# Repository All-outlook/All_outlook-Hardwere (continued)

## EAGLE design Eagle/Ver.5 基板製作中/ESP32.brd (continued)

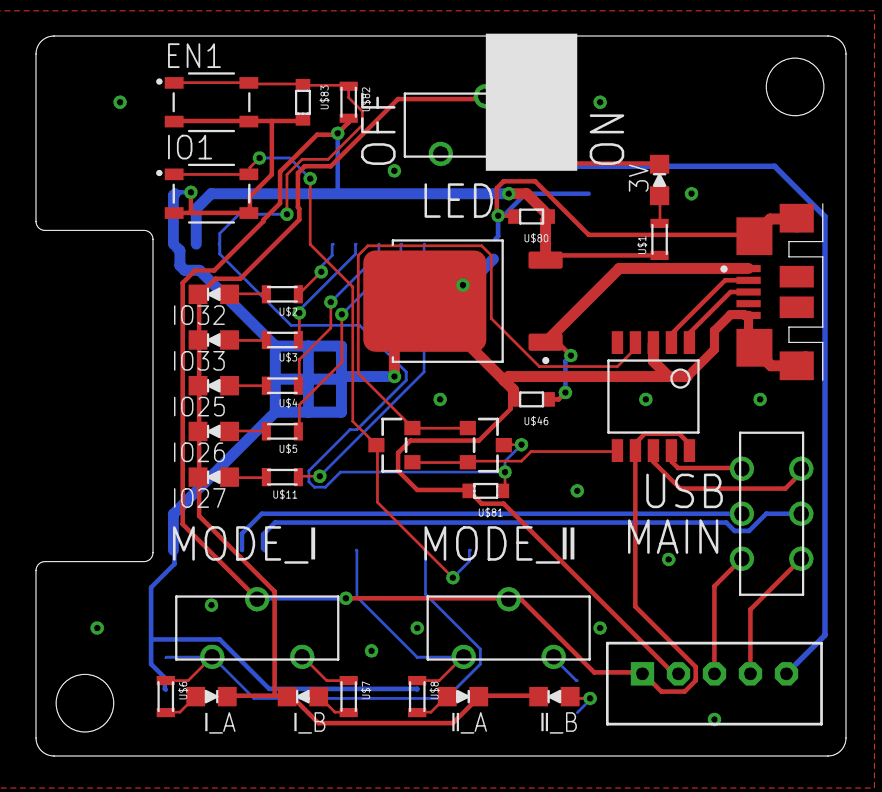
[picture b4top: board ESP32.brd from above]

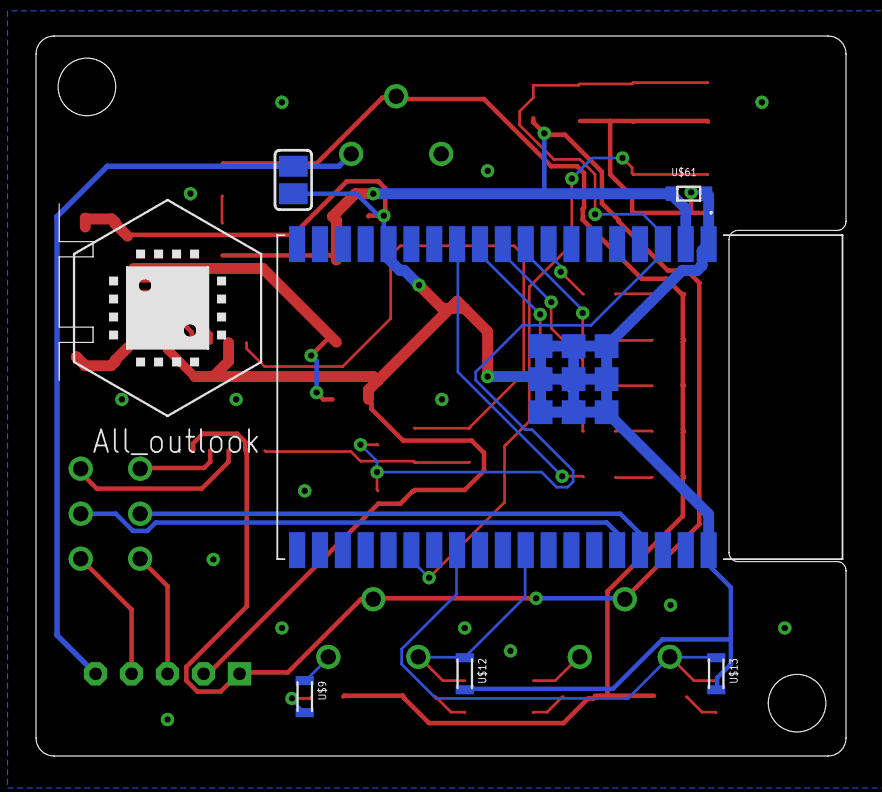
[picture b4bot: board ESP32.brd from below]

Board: 2 copper layers, 45.0 x 40.0 mm, 43 parts (7 on the bottom side), 36 nets.

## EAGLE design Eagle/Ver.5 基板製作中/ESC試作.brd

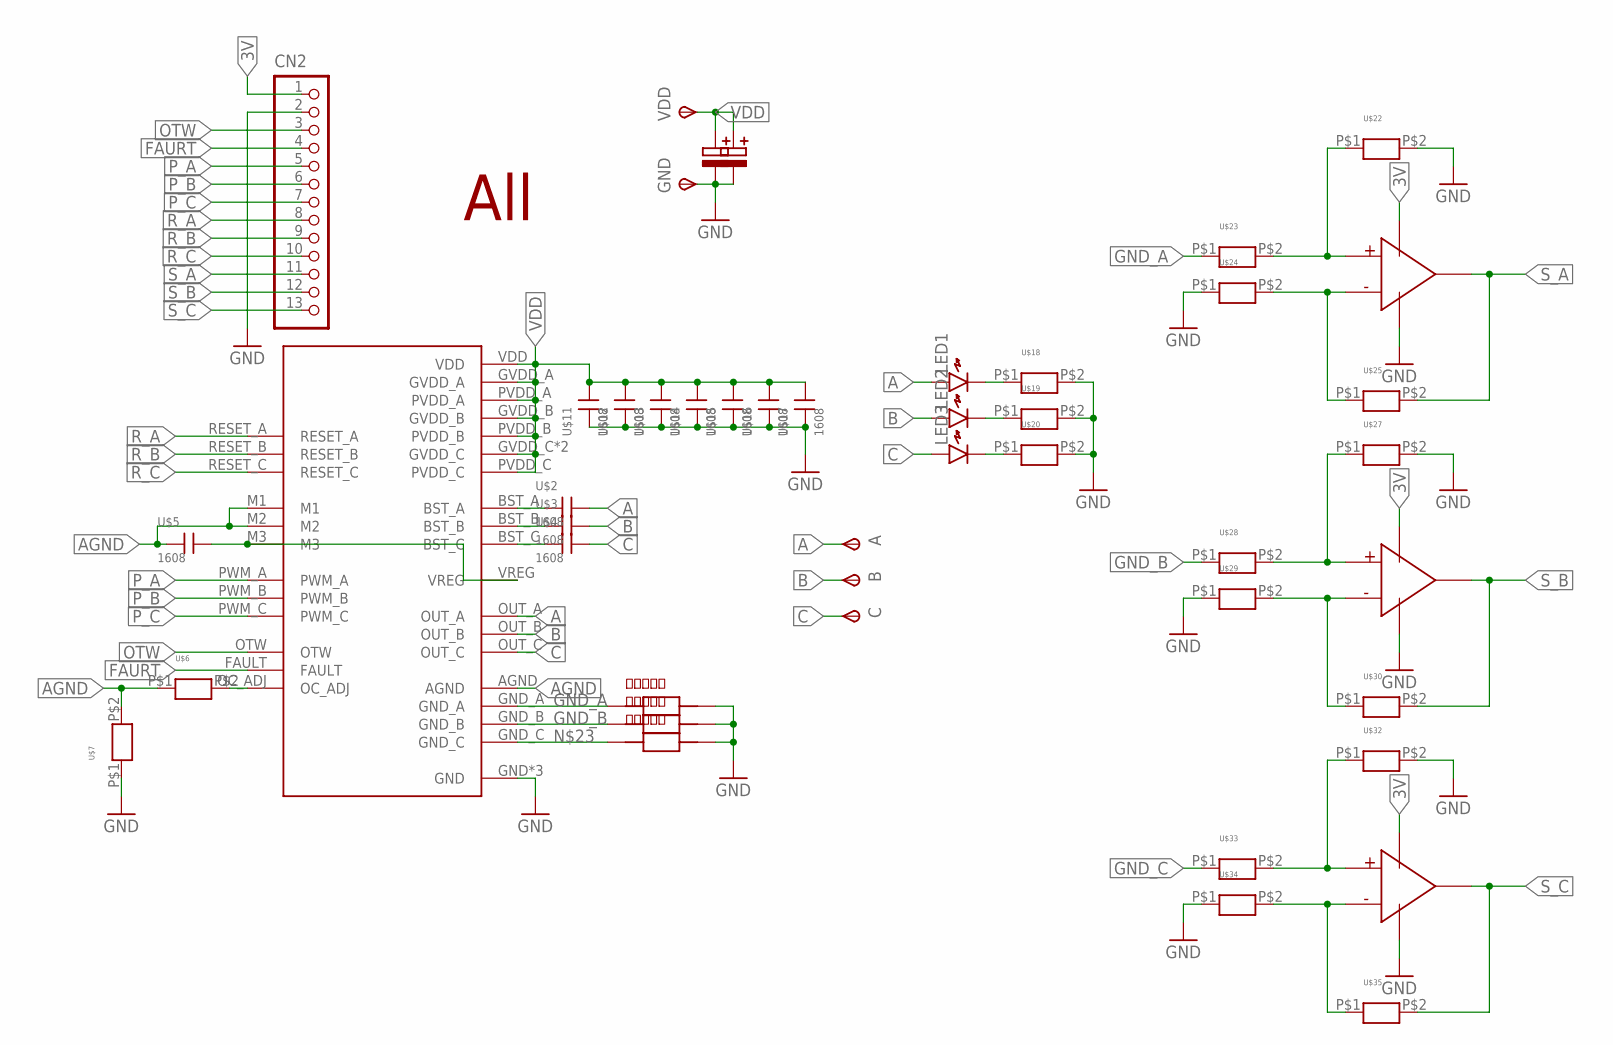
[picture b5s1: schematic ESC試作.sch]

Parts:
A: TPSPAD1-20; P1-20
B: TPSPAD1-20; P1-20
C: TPSPAD1-20; P1-20
CN2: B13B-XH-A
GND: TPSPAD1-20; P1-20
LED1, LED2, LED3: LED1608
U$1: DRV8332
U$2, U$3, U$4, U$5, U$11, U$12, U$13, U$14, U$15, U$16, U$17: 1608; CON
U$6, U$7, U$18, U$19, U$20, U$22, U$23, U$24, U$25, U$27, U$28, U$29, U$30, U$32, U$33, U$34, U$35: R; 1608
U$8, U$9, U$10: R0.1
U$21, U$26, U$31: 77701
U$36, U$37: 25V100
U$38: ALL
VDD: TPSPAD1-20; P1-20

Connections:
3V: CN2.1, U$21.VIN, U$26.VIN, U$31.VIN
A: A.TP, LED1.A, U$1.OUT_A, U$2.P$1 (1)
AGND: U$1.AGND, U$1.M1, U$1.M2, U$5.P$2 (2), U$6.P$1, U$7.P$2
B: B.TP, LED2.A, U$1.OUT_B, U$3.P$1 (1)
C: C.TP, LED3.A, U$1.OUT_C, U$4.P$1 (1)
FAURT: CN2.4, U$1.FAULT
GND: CN2.2, GND.TP, U$1.GND, U$1.GND1 (GND), U$1.GND2 (GND), U$7.P$1, U$8.P$2, U$9.P$2, U$10.P$2, U$11.P$2 (2), U$12.P$2 (2), U$13.P$2 (2), U$14.P$2 (2), U$15.P$2 (2), U$16.P$2 (2), U$17.P$2 (2), U$18.P$2, U$19.P$2, U$20.P$2, U$21.VOUT, U$22.P$2, U$24.P$1, U$26.VOUT, U$27.P$2, U$29.P$1, U$31.VOUT, U$32.P$2, U$34.P$1, U$36.P$2, U$37.P$2
GND_A: U$1.GND_A, U$8.P$1, U$23.P$1
GND_B: U$1.GND_B, U$9.P$1, U$28.P$1
GND_C: U$33.P$1
unnamed: U$21.+, U$22.P$1, U$23.P$2
unnamed: U$21.-, U$24.P$2, U$25.P$1
unnamed: U$1.M3, U$1.VREG, U$5.P$1 (1)
unnamed: LED3.K, U$20.P$1
unnamed: LED2.K, U$19.P$1
unnamed: LED1.K, U$18.P$1
unnamed: U$26.+, U$27.P$1, U$28.P$2
unnamed: U$26.-, U$29.P$2, U$30.P$1
unnamed: U$31.+, U$32.P$1, U$33.P$2
unnamed: U$31.-, U$34.P$2, U$35.P$1
unnamed: U$1.GND_C, U$10.P$1
unnamed: U$1.BST_A, U$2.P$2 (2)
unnamed: U$1.BST_B, U$3.P$2 (2)
unnamed: U$1.BST_C, U$4.P$2 (2)
unnamed: U$1.OC_ADJ, U$6.P$2
OTW: CN2.3, U$1.OTW
P_A: CN2.5, U$1.PWM_A
P_B: CN2.6, U$1.PWM_B
P_C: CN2.7, U$1.PWM_C
R_A: CN2.8, U$1.RESET_A
R_B: CN2.9, U$1.RESET_B
R_C: CN2.10, U$1.RESET_C
S_A: CN2.11, U$21.O, U$25.P$2
S_B: CN2.12, U$26.O, U$30.P$2
S_C: CN2.13, U$31.O, U$35.P$2
VDD: U$1.GVDD_A, U$1.GVDD_B, U$1.GVDD_C, U$1.GVDD_C2 (GVDD_C), U$1.PVDD_A, U$1.PVDD_B, U$1.PVDD_C, U$1.VDD, U$11.P$1 (1), U$12.P$1 (1), U$13.P$1 (1), U$14.P$1 (1), U$15.P$1 (1), U$16.P$1 (1), U$17.P$1 (1), U$36.P$1, U$37.P$1, VDD.TP

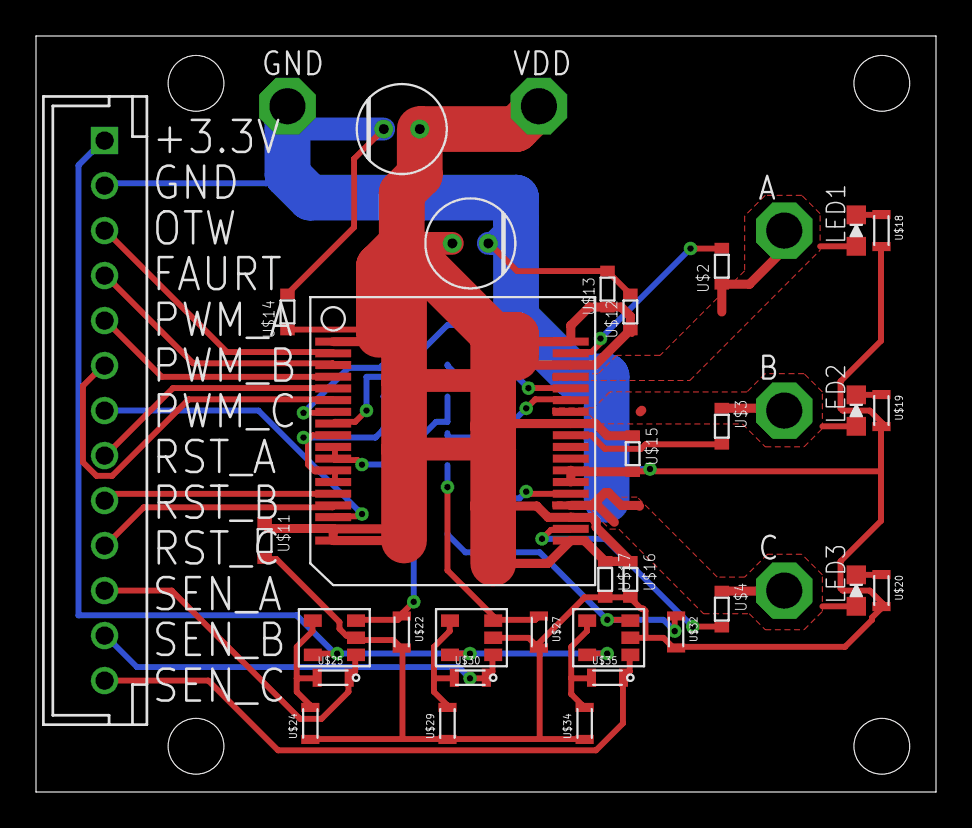
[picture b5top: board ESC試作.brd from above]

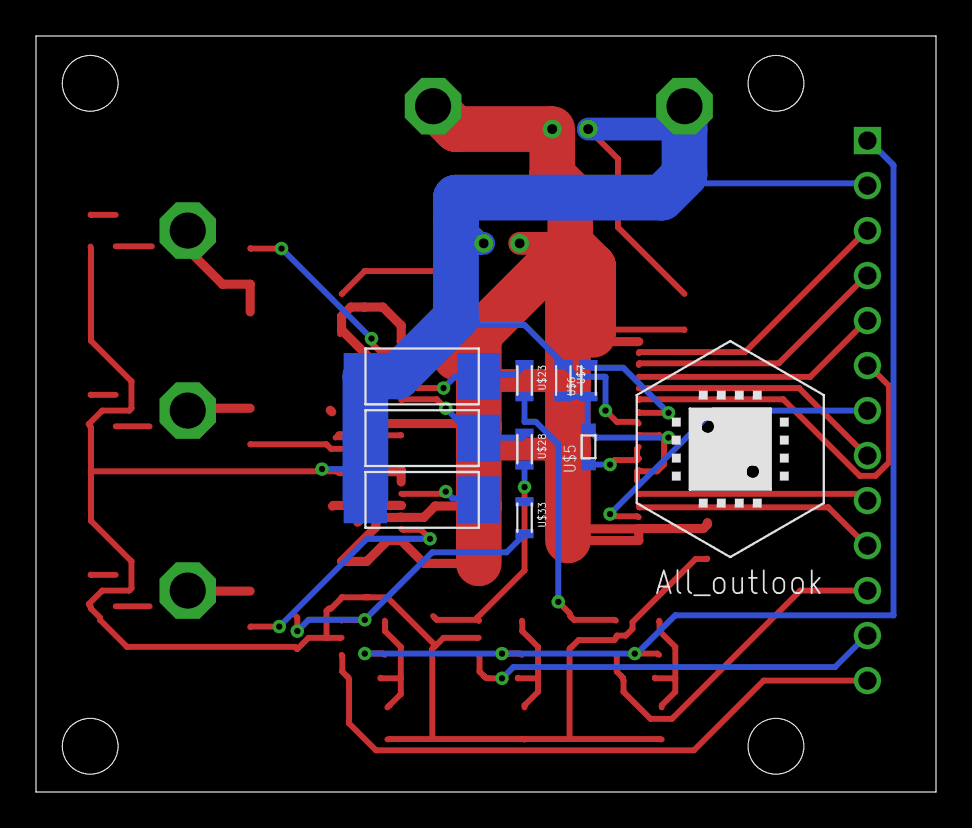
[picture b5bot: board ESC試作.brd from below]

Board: 2 copper layers, 50.0 x 42.0 mm, 47 parts (10 on the bottom side), 35 nets.

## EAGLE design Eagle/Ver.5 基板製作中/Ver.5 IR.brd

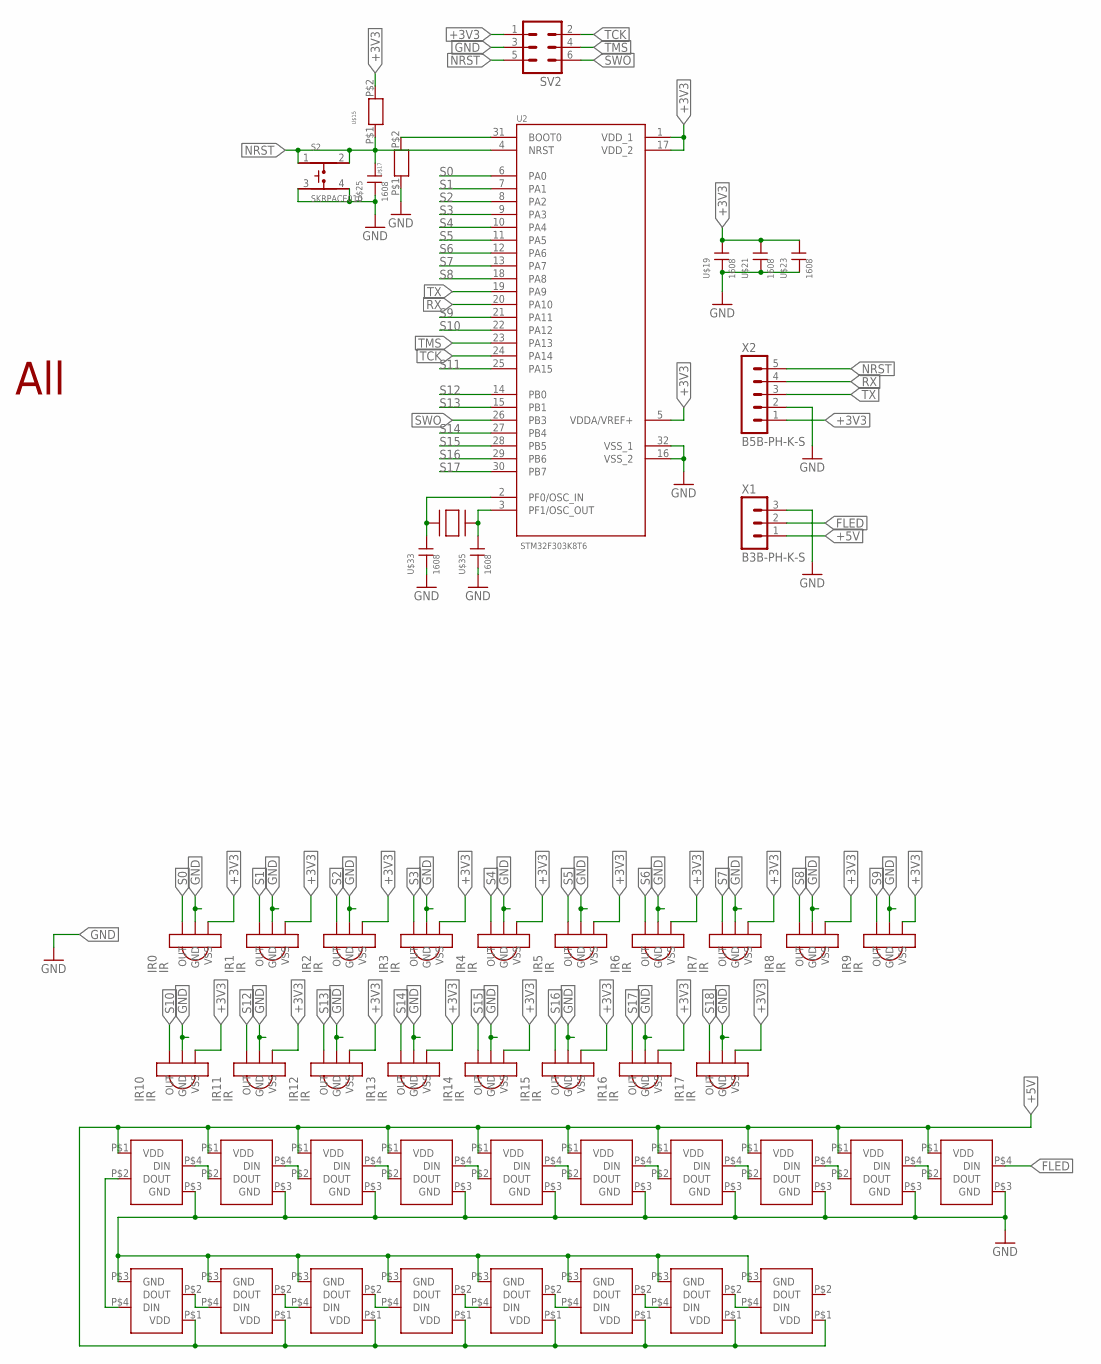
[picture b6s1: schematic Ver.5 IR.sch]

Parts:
F0, F1, F2, F3, F4, F5, F6, F7, F8, F9, F10, F11, F12, F13, F14, F15, F16, F17: LED
IR0, IR1, IR2, IR3, IR4, IR5, IR6, IR7, IR8, IR9, IR10, IR11, IR12, IR13, IR14, IR15, IR16, IR17: IR
S2: SKRPACE010; SW_SKRPACE010
SV2: ML6
U2: STM32F303K8T6; QFP80P900X900X160-32N
U$1: ALL
U$15, U$17: R; 1608
U$19, U$21, U$23, U$25, U$33, U$35: 1608; CON
U$27: SUISYOU; 水晶
X1: B3B-PH-K-S
X2: B5B-PH-K-S

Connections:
+3V3: IR0.P$3 (VSS), IR1.P$3 (VSS), IR2.P$3 (VSS), IR3.P$3 (VSS), IR4.P$3 (VSS), IR5.P$3 (VSS), IR6.P$3 (VSS), IR7.P$3 (VSS), IR8.P$3 (VSS), IR9.P$3 (VSS), IR10.P$3 (VSS), IR11.P$3 (VSS), IR12.P$3 (VSS), IR13.P$3 (VSS), IR14.P$3 (VSS), IR15.P$3 (VSS), IR16.P$3 (VSS), IR17.P$3 (VSS), SV2.1, U2.1 (VDD_1), U2.5 (VDDA/VREF+), U2.17 (VDD_2), U$15.P$2, U$19.P$1 (1), U$21.P$1 (1), U$23.P$1 (1), X2.1
+5V: F0.P$1 (VDD), F1.P$1 (VDD), F2.P$1 (VDD), F3.P$1 (VDD), F4.P$1 (VDD), F5.P$1 (VDD), F6.P$1 (VDD), F7.P$1 (VDD), F8.P$1 (VDD), F9.P$1 (VDD), F10.P$1 (VDD), F11.P$1 (VDD), F12.P$1 (VDD), F13.P$1 (VDD), F14.P$1 (VDD), F15.P$1 (VDD), F16.P$1 (VDD), F17.P$1 (VDD), X1.1
FLED: F0.P$4 (DIN), X1.2
GND: F0.P$3 (GND), F1.P$3 (GND), F2.P$3 (GND), F3.P$3 (GND), F4.P$3 (GND), F5.P$3 (GND), F6.P$3 (GND), F7.P$3 (GND), F8.P$3 (GND), F9.P$3 (GND), F10.P$3 (GND), F11.P$3 (GND), F12.P$3 (GND), F13.P$3 (GND), F14.P$3 (GND), F15.P$3 (GND), F16.P$3 (GND), F17.P$3 (GND), IR0.P$2 (GND), IR1.P$2 (GND), IR2.P$2 (GND), IR3.P$2 (GND), IR4.P$2 (GND), IR5.P$2 (GND), IR6.P$2 (GND), IR7.P$2 (GND), IR8.P$2 (GND), IR9.P$2 (GND), IR10.P$2 (GND), IR11.P$2 (GND), IR12.P$2 (GND), IR13.P$2 (GND), IR14.P$2 (GND), IR15.P$2 (GND), IR16.P$2 (GND), IR17.P$2 (GND), S2.3, S2.4, SV2.3, U2.16 (VSS_2), U2.32 (VSS_1), U$17.P$1, U$19.P$2 (2), U$21.P$2 (2), U$23.P$2 (2), U$25.P$2 (2), U$33.P$2 (2), U$35.P$2 (2), X1.3, X2.2
unnamed: F14.P$2 (DOUT), F15.P$4 (DIN)
unnamed: F13.P$2 (DOUT), F14.P$4 (DIN)
unnamed: F11.P$2 (DOUT), F12.P$4 (DIN)
unnamed: F10.P$2 (DOUT), F11.P$4 (DIN)
unnamed: F8.P$2 (DOUT), F9.P$4 (DIN)
unnamed: F7.P$2 (DOUT), F8.P$4 (DIN)
unnamed: F5.P$2 (DOUT), F6.P$4 (DIN)
unnamed: F4.P$2 (DOUT), F5.P$4 (DIN)
unnamed: F2.P$2 (DOUT), F3.P$4 (DIN)
unnamed: F1.P$2 (DOUT), F2.P$4 (DIN)
unnamed: F0.P$2 (DOUT), F1.P$4 (DIN)
unnamed: F3.P$2 (DOUT), F4.P$4 (DIN)
unnamed: F6.P$2 (DOUT), F7.P$4 (DIN)
unnamed: F9.P$2 (DOUT), F10.P$4 (DIN)
unnamed: F16.P$2 (DOUT), F17.P$4 (DIN)
unnamed: F15.P$2 (DOUT), F16.P$4 (DIN)
unnamed: F12.P$2 (DOUT), F13.P$4 (DIN)
unnamed: U2.31 (BOOT0), U$17.P$2
unnamed: U2.2 (PF0/OSC_IN), U$27.P$1, U$33.P$1 (1)
unnamed: U2.3 (PF1/OSC_OUT), U$27.P$2, U$35.P$1 (1)
NRST: S2.1, S2.2, SV2.5, U2.4 (NRST), U$15.P$1, U$25.P$1 (1), X2.5
RX: U2.20 (PA10), X2.4
S0: IR0.P$1 (OUT), U2.6 (PA0)
S1: IR1.P$1 (OUT), U2.7 (PA1)
S2: IR2.P$1 (OUT), U2.8 (PA2)
S3: IR3.P$1 (OUT), U2.9 (PA3)
S4: IR4.P$1 (OUT), U2.10 (PA4)
S5: IR5.P$1 (OUT), U2.11 (PA5)
S6: IR6.P$1 (OUT), U2.12 (PA6)
S7: IR7.P$1 (OUT), U2.13 (PA7)
S8: IR8.P$1 (OUT), U2.18 (PA8)
S9: IR9.P$1 (OUT), U2.21 (PA11)
S10: IR10.P$1 (OUT), U2.22 (PA12)
S11: U2.25 (PA15)
S12: IR11.P$1 (OUT), U2.14 (PB0)
S13: IR12.P$1 (OUT), U2.15 (PB1)
S14: IR13.P$1 (OUT), U2.27 (PB4)
S15: IR14.P$1 (OUT), U2.28 (PB5)
S16: IR15.P$1 (OUT), U2.29 (PB6)
S17: IR16.P$1 (OUT), U2.30 (PB7)
S18: IR17.P$1 (OUT)
SWO: SV2.6, U2.26 (PB3)
TCK: SV2.2, U2.24 (PA14)
TMS: SV2.4, U2.23 (PA13)
TX: U2.19 (PA9), X2.3

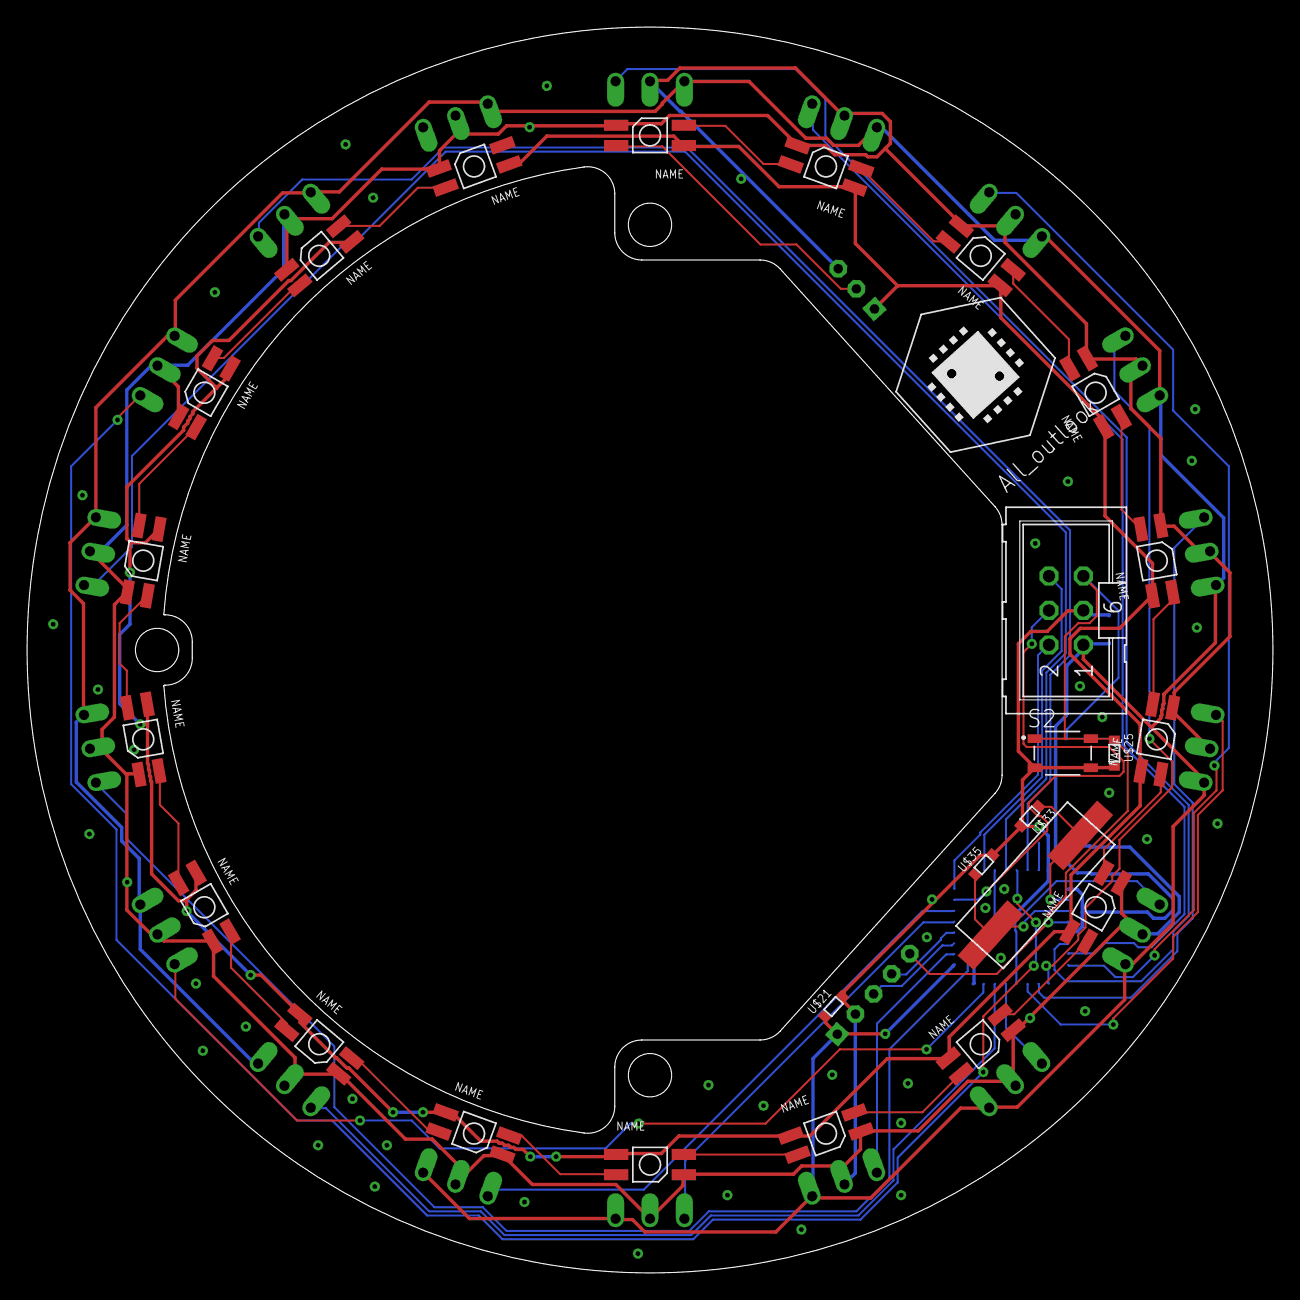
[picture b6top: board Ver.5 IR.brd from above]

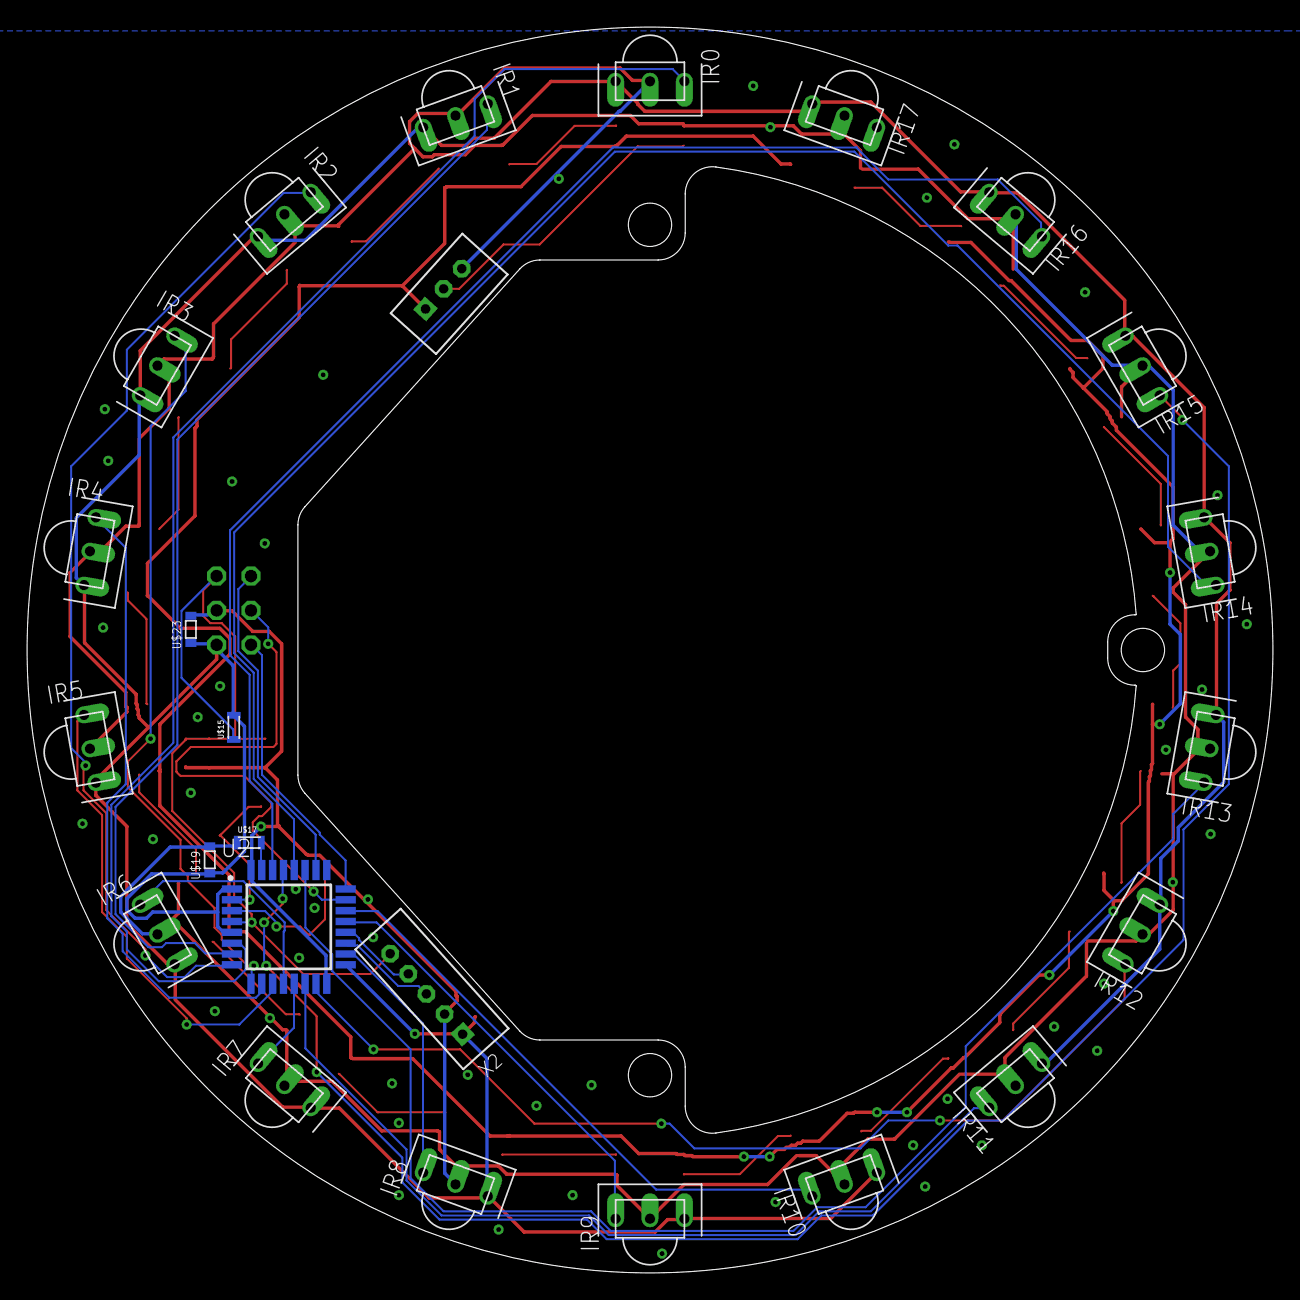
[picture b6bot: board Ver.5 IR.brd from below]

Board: 2 copper layers, 92.0 x 92.0 mm, 51 parts (25 on the bottom side), 47 nets.

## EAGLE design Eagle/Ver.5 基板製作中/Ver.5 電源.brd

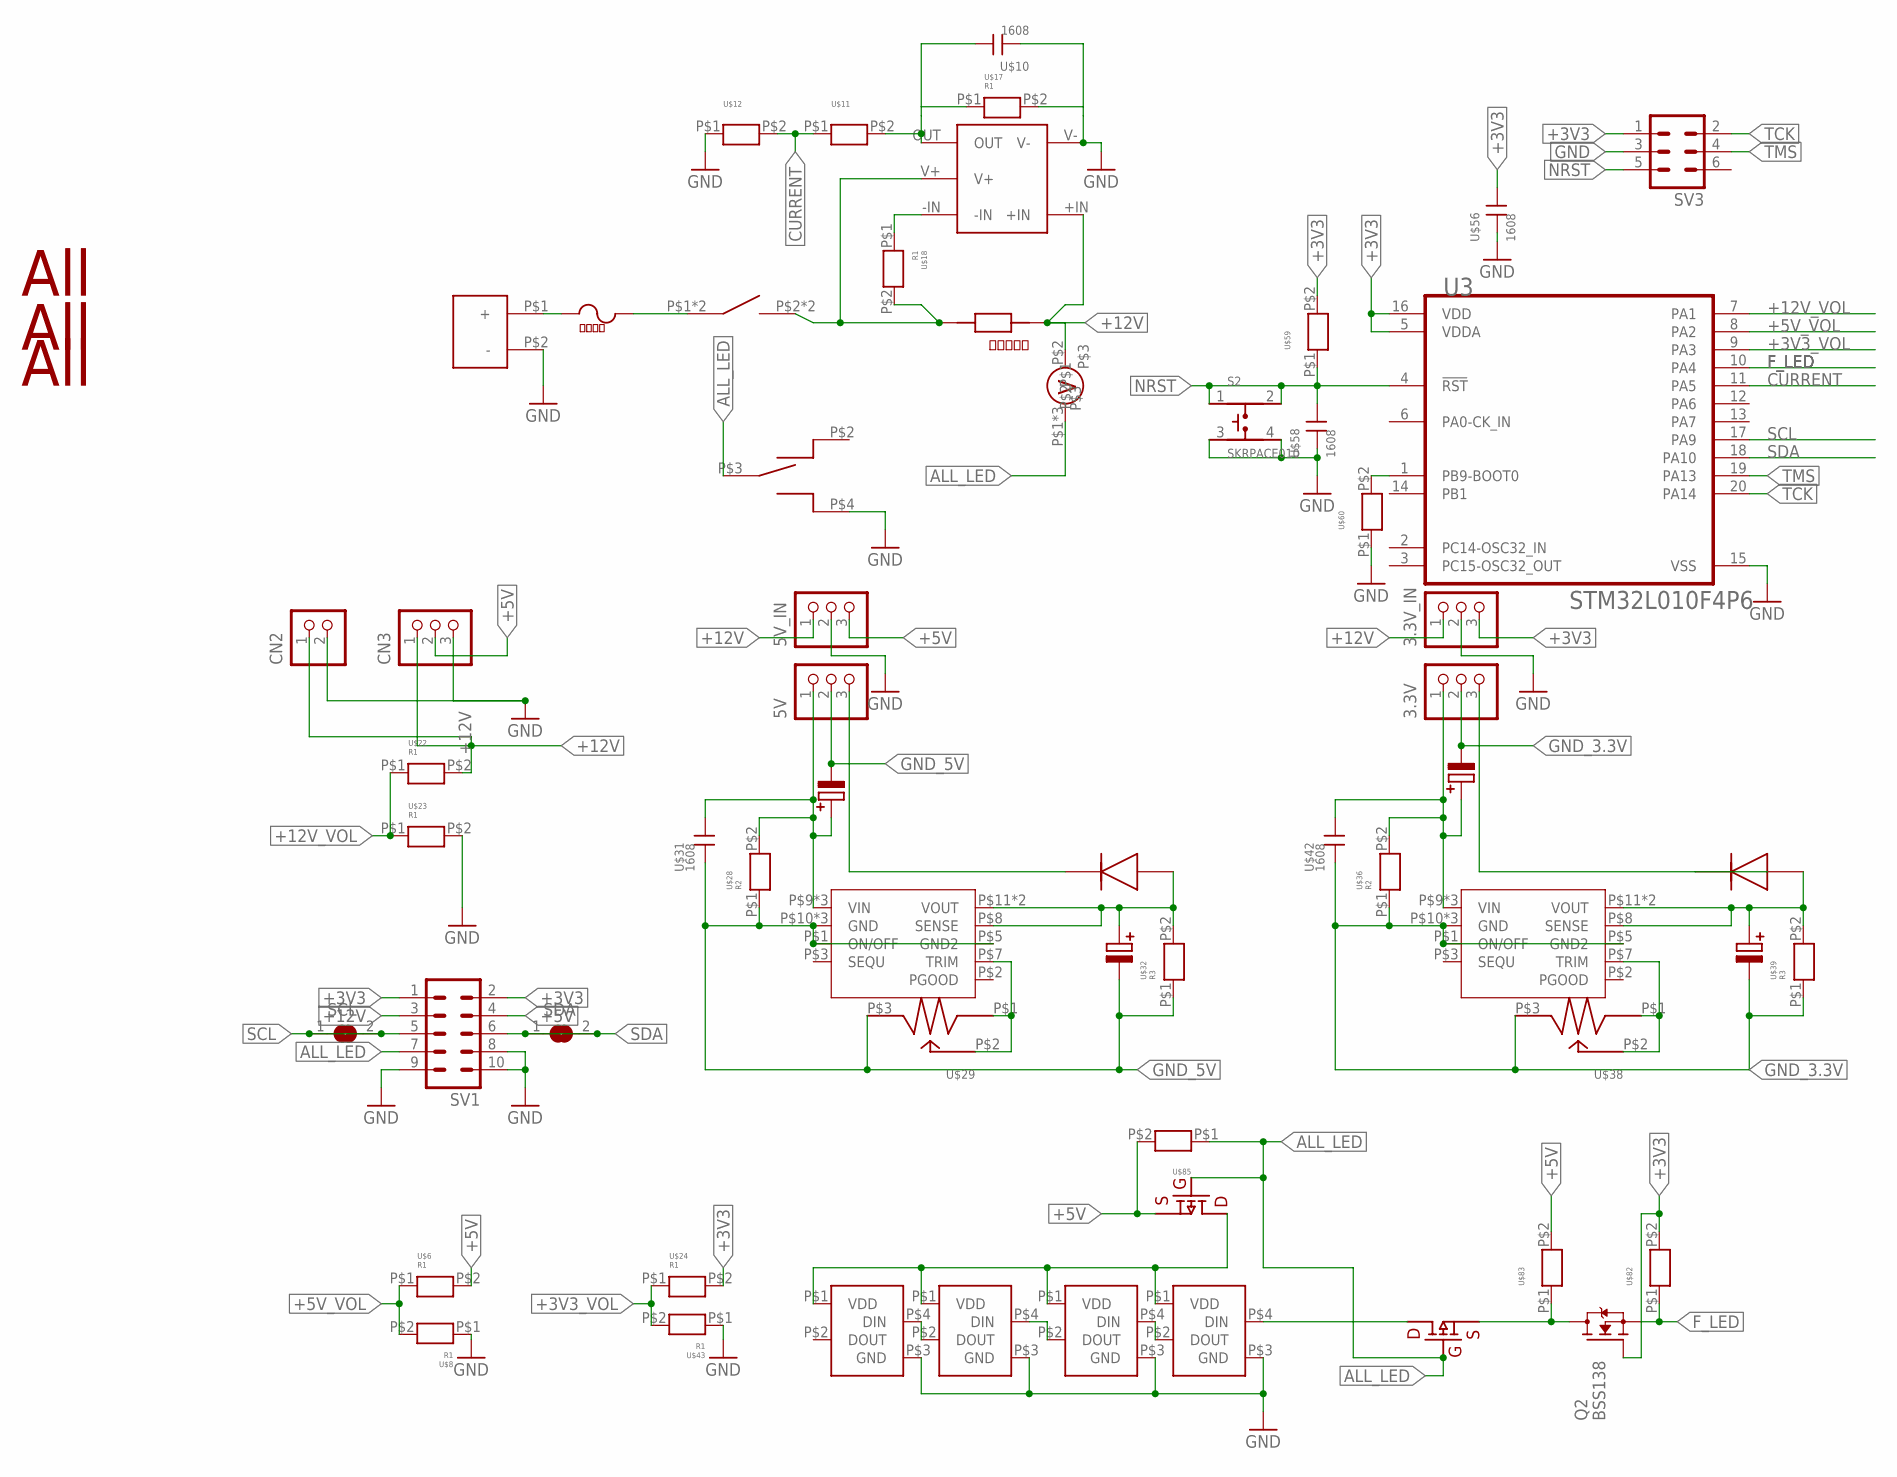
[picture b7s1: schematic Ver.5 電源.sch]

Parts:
3.3V, 3.3V_IN, 5V, 5V_IN: B3B-XH-A
CN2: B2B-XH-A
CN3: B3B-XH-A
F1, F2, F3, F18: LED
Q2: BSS138; SOT23
S2: SKRPACE010; SW_SKRPACE010
SCL: SJ
SDA: SJ
SV1: ML10
SV3: ML6
U3: STMICROELECTRONICS_STM32L010F4P6STMICROELECTRONIC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; STMICROELECTRONICS_STM32L010F4P6_0
U$1: XT60
U$2: MF; ｍｆ
U$3: V
U$4: SW3
U$5, U$7, U$30, U$40: 25V100
U$6, U$8, U$17, U$18, U$22, U$23, U$24, U$43: R1; 1608
U$9, U$15, U$19: ALL
U$10, U$31, U$42, U$56, U$58: 1608; CON
U$11, U$12, U$59, U$60, U$82, U$83, U$85: R; 1608
U$13: LT6106
U$14: R; ｒ05
U$16: S
U$26, U$34: DCDC; DC-DC
U$28, U$36: R2; 1608
U$29, U$38: VR
U$32, U$39: R3; 1608
U$33, U$37: 40V5A
U$84, U$86: 808

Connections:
+3V3: 3.3V_IN.3, Q2.1 (G), SV1.1, SV1.2, SV3.1, U3.5 (VDDA), U3.16 (VDD), U$24.P$2, U$56.P$1 (1), U$59.P$2, U$82.P$2
+3V3_VOL: U3.9 (PA3), U$24.P$1, U$43.P$2
+5V: 5V_IN.3, CN3.2, SV1.4, U$6.P$2, U$83.P$2, U$84.S, U$85.P$2
+5V_OFF1: F1.P$1 (VDD), F2.P$1 (VDD), F3.P$1 (VDD), F18.P$1 (VDD), U$84.D, U$84.DD (D), U$84.DDD (D), U$84.DDDD (D)
+5V_VOL: U3.8 (PA2), U$6.P$1, U$8.P$2
+12V: 3.3V_IN.1, 5V_IN.1, CN2.1, CN3.1, SV1.3, U$3.P$2, U$13.+IN, U$14.P$1, U$22.P$2
+12V_VOL: U3.7 (PA1), U$22.P$1, U$23.P$1
ALL_LED: SV1.7, U$3.P$1, U$3.P$4, U$3.P$5, U$16.P$3 (2), U$84.G, U$85.P$1, U$86.G
CURRENT: U3.11 (PA5), U$11.P$1, U$12.P$2
F_LED: Q2.2 (S), U3.10 (PA4), U$82.P$1
GND: 3.3V_IN.2, 5V_IN.2, CN2.2, CN3.3, F1.P$3 (GND), F2.P$3 (GND), F3.P$3 (GND), F18.P$3 (GND), S2.3, S2.4, SV1.8, SV1.9, SV1.10, SV3.3, U3.15 (VSS), U$1.P$2 (-), U$8.P$1, U$10.P$2 (2), U$12.P$1, U$13.V-, U$16.P$4 (3), U$17.P$2, U$23.P$2, U$43.P$1, U$56.P$2 (2), U$58.P$2 (2), U$60.P$1
GND_3.3V: 3.3V.2, U$7.P$2, U$34.P$1 (ON/OFF), U$34.P$5 (GND2), U$34.P$10 (GND), U$34.P$16 (GND), U$34.P$17 (GND), U$36.P$1, U$38.P$3, U$39.P$1, U$40.P$2, U$42.P$2 (2)
GND_5V: 5V.2, U$5.P$2, U$26.P$1 (ON/OFF), U$26.P$5 (GND2), U$26.P$10 (GND), U$26.P$16 (GND), U$26.P$17 (GND), U$28.P$1, U$29.P$3, U$30.P$2, U$31.P$2 (2), U$32.P$1
unnamed: U$10.P$1 (1), U$11.P$2, U$13.OUT, U$17.P$1
unnamed: F2.P$2 (DOUT), F3.P$4 (DIN)
unnamed: U$1.P$1 (+), U$2.P$1, U$2.P$2
unnamed: U$2.P$3, U$2.P$4, U$4.P$1, U$4.P$3
unnamed: F1.P$2 (DOUT), F2.P$4 (DIN)
unnamed: F1.P$4 (DIN), F18.P$2 (DOUT)
unnamed: 5V.1, U$5.P$1, U$26.P$9 (VIN), U$26.P$14 (VIN), U$26.P$15 (VIN), U$28.P$2, U$31.P$1 (1)
unnamed: U$13.-IN, U$18.P$1
unnamed: 3.3V.1, U$7.P$1, U$34.P$9 (VIN), U$34.P$14 (VIN), U$34.P$15 (VIN), U$36.P$2, U$42.P$1 (1)
unnamed: 5V.3, U$33.P$2
unnamed: U$4.P$2, U$4.P$4, U$13.V+, U$14.P$2, U$18.P$2
unnamed: 3.3V.3, U$37.P$2
unnamed: U3.1 (PB9-BOOT0), U$60.P$2
unnamed: U$26.P$8 (SENSE), U$26.P$11 (VOUT), U$26.P$18 (VOUT), U$30.P$1, U$32.P$2, U$33.P$1
unnamed: U$26.P$7 (TRIM), U$29.P$1, U$29.P$2
unnamed: U$34.P$8 (SENSE), U$34.P$11 (VOUT), U$34.P$18 (VOUT), U$37.P$1, U$39.P$2, U$40.P$1
unnamed: U$34.P$7 (TRIM), U$38.P$1, U$38.P$2
unnamed: Q2.3 (D), U$83.P$1, U$86.S
unnamed: F18.P$4 (DIN), U$86.D, U$86.DD (D), U$86.DDD (D), U$86.DDDD (D)
NRST: S2.1, S2.2, SV3.5, U3.4 (!RST!), U$58.P$1 (1), U$59.P$1
SCL: SCL.1, SCL.2, SV1.5, U3.17 (PA9)
SDA: SDA.1, SDA.2, SV1.6, U3.18 (PA10)
TCK: SV3.2, U3.20 (PA14)
TMS: SV3.4, U3.19 (PA13)

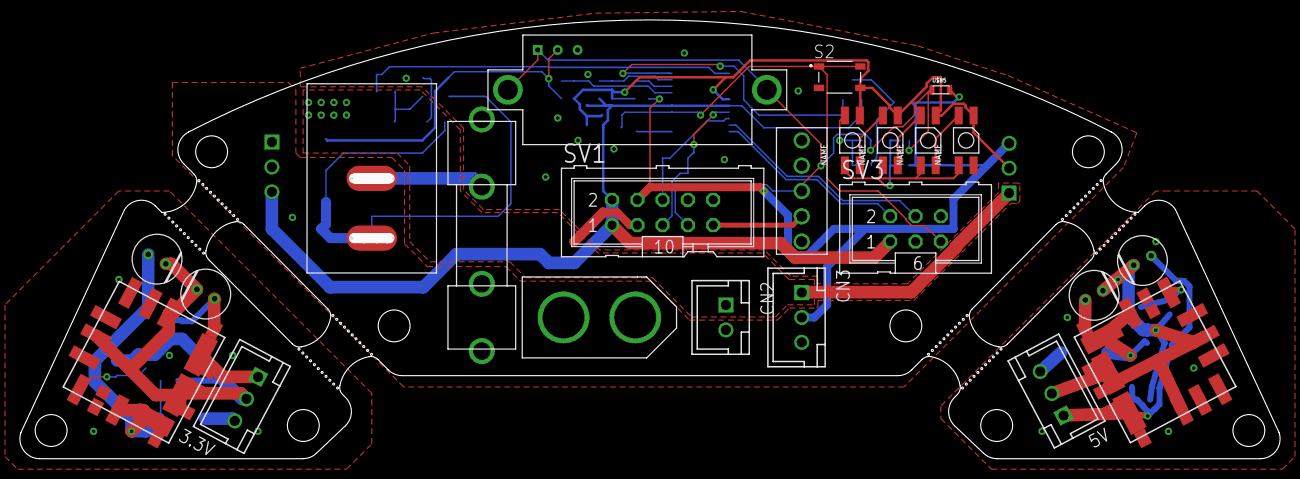
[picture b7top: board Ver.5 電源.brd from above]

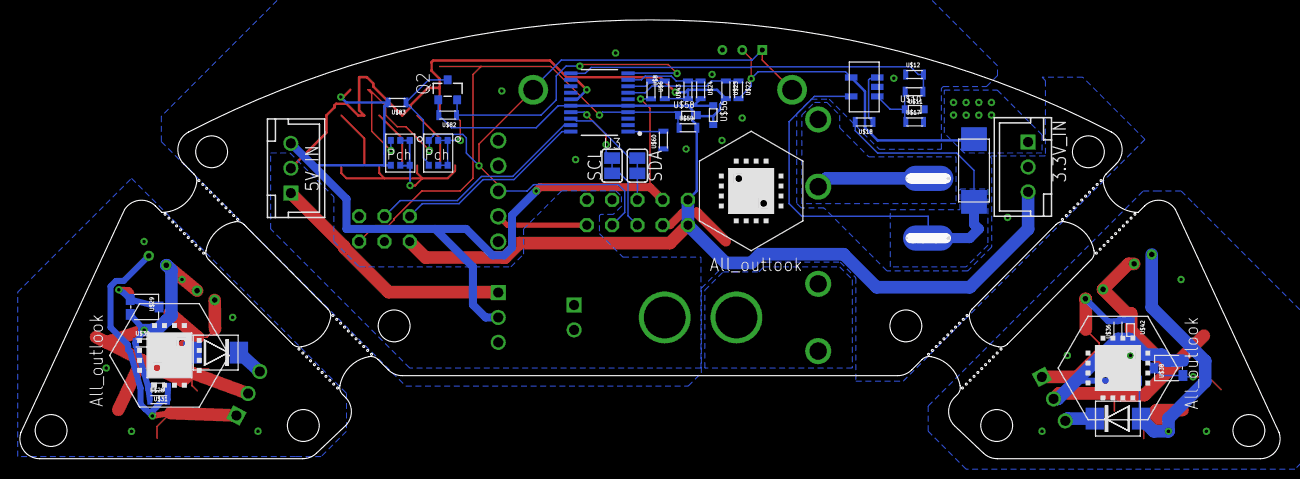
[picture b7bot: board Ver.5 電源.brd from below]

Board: 2 copper layers, 126.6 x 44.1 mm, 63 parts (40 on the bottom side), 37 nets.
